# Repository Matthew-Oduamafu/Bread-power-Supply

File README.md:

# Breadboard Power Supply

A compact and versatile power supply designed specifically for breadboard prototyping. This PCB provides multiple regulated voltage outputs (3.3V, 5V, and 12V) from a single DC barrel jack input, making it ideal for electronics hobbyists and students.

## Features

- **Multiple Voltage Outputs**: Provides 3.3V, 5V, and 12V regulated outputs
- **DC Barrel Jack Input**: Standard barrel jack connector with internal switch for easy power connection
- **Breadboard Compatible**: Designed to fit directly onto standard breadboards
- **Compact Design**: Small form factor optimized for breadboard use
- **Regulated Power**: Ensures stable voltage outputs for sensitive electronic components

## Schematic

The schematic shows the complete circuit design including voltage regulators and power distribution.

## PCB Layout

The PCB layout displays the copper traces, component placement, and board dimensions.

## 3D View

A rendered 3D visualization of the assembled PCB showing component placement and board appearance.

## Specifications

- **Input Voltage**: 12V DC (via barrel jack)
- **Output Voltages**: 
  - 3.3V regulated output
  - 5V regulated output
  - 12V pass-through
- **PCB Design**: KiCad 9.0
- **Board Type**: 2-layer PCB
- **Project Version**: Version 1

## Getting Started

### Prerequisites

- KiCad 9.0 or later (for viewing/editing the design files)
- PCB manufacturing service (for fabrication)
- Required components (see BOM - Bill of Materials)

### Opening the Project

1. Install [KiCad](https://www.kicad.org/) version 9.0 or later
2. Clone this repository
3. Open the project file: `Bread power Supply.kicad_pro`
4. View the schematic: `Bread power Supply.kicad_sch`
5. View the PCB layout: `Bread power Supply.kicad_pcb`

### Manufacturing

1. Export Gerber files from KiCad
2. Send to your preferred PCB manufacturer
3. Assemble components according to the schematic
4. Test voltage outputs before connecting to sensitive electronics

## Project Files

- `Bread power Supply.kicad_pro` - KiCad project file
- `Bread power Supply.kicad_sch` - Schematic file
- `Bread power Supply.kicad_pcb` - PCB layout file
- `pcb schematic.png` - Schematic diagram image
- `pcb layout.png` - PCB layout image
- `pcb 3d view.png` - 3D rendered view

## Usage

1. Connect a 12V DC power supply to the barrel jack connector
2. The power switch on the barrel jack controls the entire board
3. Connect your breadboard circuits to the appropriate voltage outputs:
   - Use 3.3V for low-voltage ICs and sensors
   - Use 5V for standard logic circuits and microcontrollers
   - Use 12V for motors or other higher-voltage components
4. Ensure your load does not exceed the current ratings of the voltage regulators

## Safety Notes

⚠️ **Important Safety Information:**
- Always check voltage outputs with a multimeter before connecting sensitive components
- Ensure proper heat dissipation for voltage regulators under load
- Do not exceed the maximum current ratings of the voltage regulators
- Use appropriate fusing on the input for overcurrent protection

## Author

**Matthew**

## Date

December 19, 2025

## License

This project is open-source hardware. Please check with the author for specific licensing terms.

---

*Designed with KiCad 9.0*

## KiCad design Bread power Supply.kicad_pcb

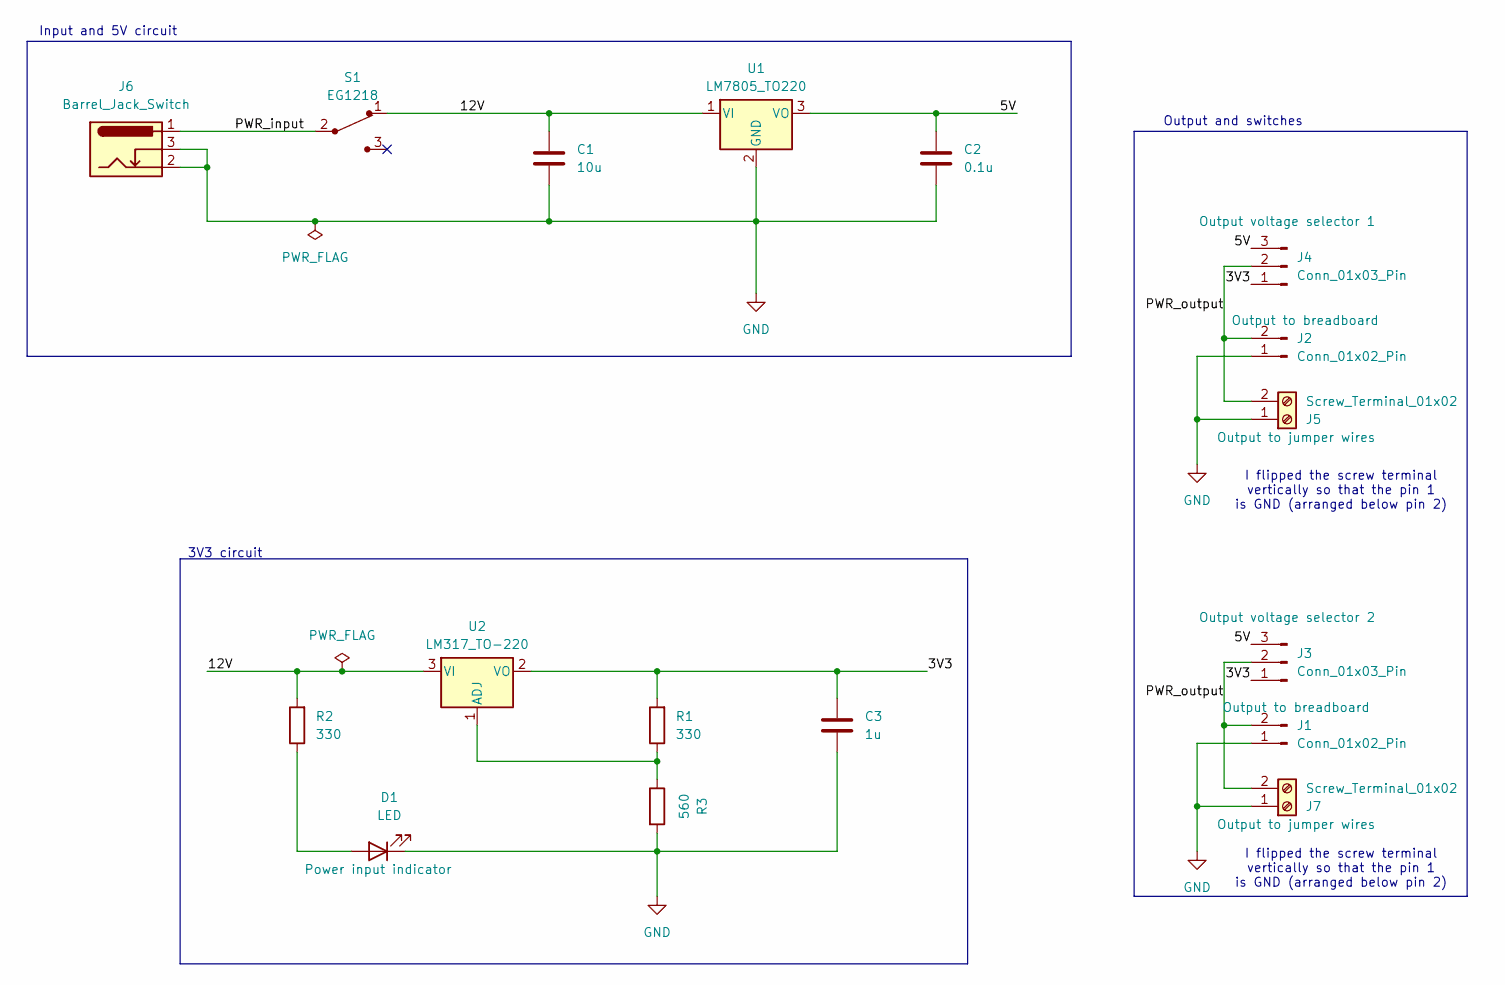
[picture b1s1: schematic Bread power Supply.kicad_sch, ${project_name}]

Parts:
C1: 10u; C_Disc_D3.0mm_W1.6mm_P2.50mm
C2: 0.1u; C_Disc_D3.0mm_W1.6mm_P2.50mm
C3: 1u; C_Disc_D3.0mm_W1.6mm_P2.50mm
D1: LED; LED_D5.0mm
J1, J2: Conn_01x02_Pin; PinHeader_1x02_P2.54mm_Vertical
J3, J4: Conn_01x03_Pin; PinHeader_1x03_P2.54mm_Vertical
J5, J7: Screw_Terminal_01x02; TerminalBlock_MaiXu_MX126-5.0-02P_1x02_P5.00mm
J6: Barrel_Jack_Switch; BarrelJack_Horizontal
R1, R2: 330; R_Axial_DIN0204_L3.6mm_D1.6mm_P7.62mm_Horizontal
R3: 560; R_Axial_DIN0204_L3.6mm_D1.6mm_P7.62mm_Horizontal
S1: EG1218; Switch_Slide_11.6x4mm_EG1218; MPN EG1218; Digi-Key_PN EG1903-ND
U1: LM7805_TO220; TO-220-3_Vertical
U2: LM317_TO-220; TO-220-3_Vertical

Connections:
/3V3: C3.2, J3.1, J4.1, R1.2, U2.2 (VO)
/5V: C2.1, J3.3, J4.3, U1.3 (VO)
/12V: C1.1, R2.2, S1.1, U1.1 (VI), U2.3 (VI)
/PWR_input: J6.1, S1.2
/PWR_output: J1.2, J2.2, J3.2, J4.2, J5.2, J7.2
GND: C1.2, C2.2, C3.1, D1.1 (K), J1.1, J2.1, J5.1, J6.2, J6.3, J7.1, R3.2, U1.2 (GND)
unnamed: D1.2 (A), R2.1
unnamed: R1.1, R3.1, U2.1 (ADJ)

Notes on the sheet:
Input and 5V circuit
3V3 circuit
I flipped the screw terminal vertically so that the pin 1 is GND (arranged below pin 2)
Output and switches

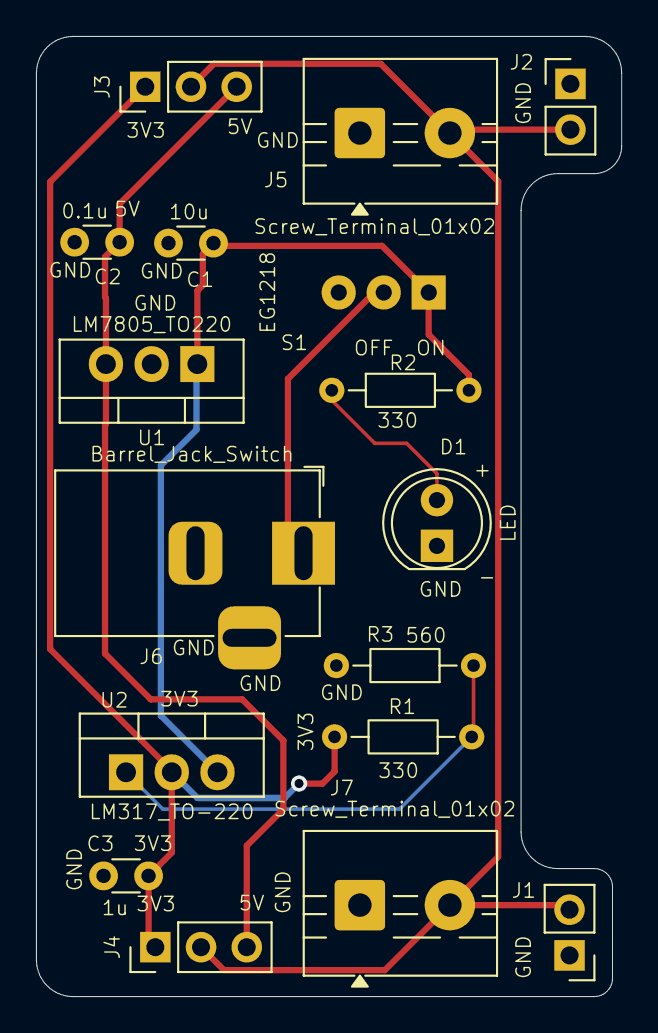
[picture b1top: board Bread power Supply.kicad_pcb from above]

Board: 2 copper layers, 32.5 x 53.3 mm, 17 parts (1 on the bottom side), 8 nets.

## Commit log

2025-12-20 Initial plan
2025-12-20 Create comprehensive README.md with project documentation and images
2025-12-25 done
